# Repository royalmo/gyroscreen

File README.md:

# Gyroscreen

(Work in progress)

A USB device that updates your screen orientation programmatically

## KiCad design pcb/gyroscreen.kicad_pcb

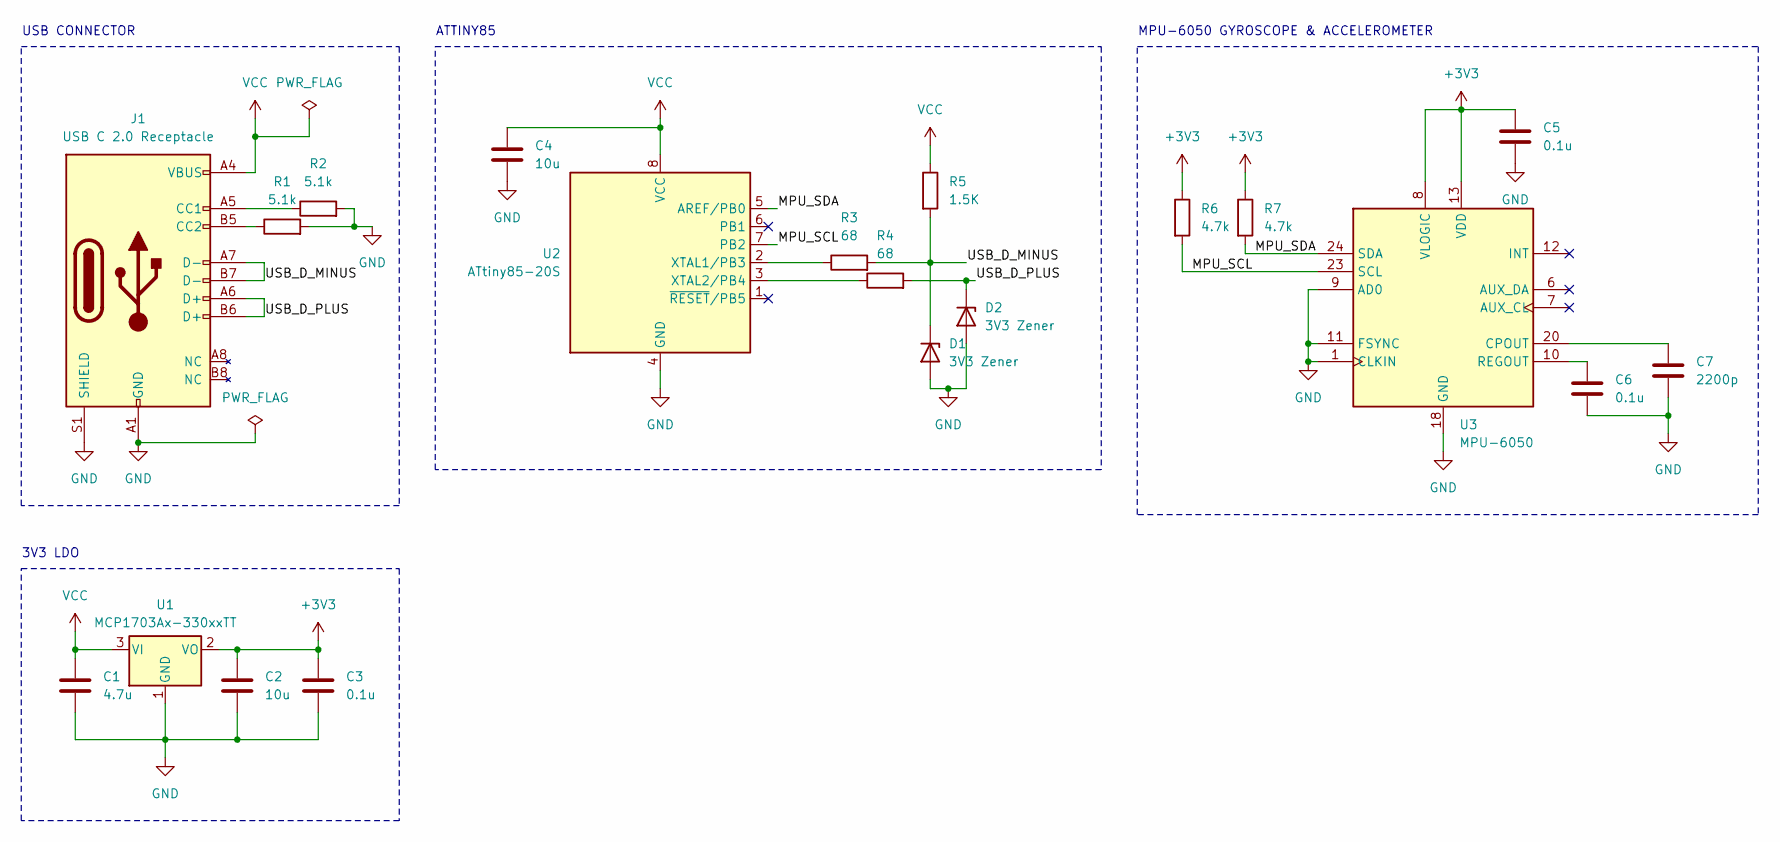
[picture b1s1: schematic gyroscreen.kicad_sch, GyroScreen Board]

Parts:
C1: 4.7u; C_0805_2012Metric_Pad1.18x1.45mm_HandSolder
C2, C4: 10u; C_0805_2012Metric_Pad1.18x1.45mm_HandSolder
C3, C5, C6: 0.1u; C_0805_2012Metric_Pad1.18x1.45mm_HandSolder
C7: 2200p; C_0805_2012Metric_Pad1.18x1.45mm_HandSolder
D1, D2: 3V3 Zener; D_SOD-123F
J1: USB C 2.0 Receptacle; USB_C_Receptacle_G-Switch_GT-USB-7010ASV
R1, R2: 5.1k; R_0805_2012Metric_Pad1.20x1.40mm_HandSolder
R3, R4: 68; R_0805_2012Metric_Pad1.20x1.40mm_HandSolder
R5: 1.5K; R_0805_2012Metric_Pad1.20x1.40mm_HandSolder
R6, R7: 4.7k; R_0805_2012Metric_Pad1.20x1.40mm_HandSolder
U1: MCP1703Ax-330xxTT; SOT-23
U2: ATtiny85-20S; SOIC-8W_5.3x5.3mm_P1.27mm
U3: MPU-6050; InvenSense_QFN-24_4x4mm_P0.5mm

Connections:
+3V3: C2.1, C3.1, C5.1, R6.1, R7.1, U1.2 (VO), U3.8 (VLOGIC), U3.13 (VDD)
/MPU_SCL: R6.2, U2.7 (PB2), U3.23 (SCL)
/MPU_SDA: R7.2, U2.5 (AREF/PB0), U3.24 (SDA)
/USB_D_MINUS: D1.1 (K), J1.A7 (D-), J1.B7 (D-), R3.2, R5.2
/USB_D_PLUS: D2.1 (K), J1.A6 (D+), J1.B6 (D+), R4.2
GND: C1.2, C2.2, C3.2, C4.2, C5.2, C6.2, C7.2, D1.2 (A), D2.2 (A), J1.A1 (GND), J1.A12 (GND), J1.B1 (GND), J1.B12 (GND), J1.S1 (SHIELD), R1.2, R2.2, U1.1 (GND), U2.4 (GND), U3.1 (CLKIN), U3.9 (AD0), U3.11 (FSYNC), U3.18 (GND)
unnamed: J1.A5 (CC1), R2.1
unnamed: J1.B5 (CC2), R1.1
unnamed: R3.1, U2.2 (XTAL1/PB3)
unnamed: R4.1, U2.3 (XTAL2/PB4)
unnamed: C7.1, U3.20 (CPOUT)
unnamed: C6.1, U3.10 (REGOUT)
VCC: C1.1, C4.1, J1.A4 (VBUS), J1.A9 (VBUS), J1.B4 (VBUS), J1.B9 (VBUS), R5.1, U1.3 (VI), U2.8 (VCC)

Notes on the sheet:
MPU-6050 GYROSCOPE & ACCELEROMETER
USB CONNECTOR
ATTINY85
3V3 LDO

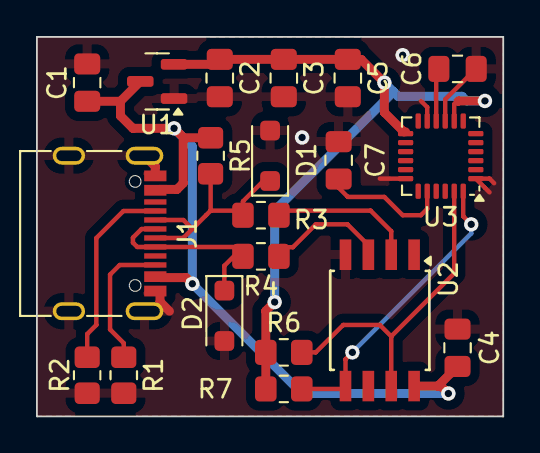
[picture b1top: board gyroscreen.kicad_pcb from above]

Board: 2 copper layers, 25.9 x 21.1 mm, 20 parts (0 on the bottom side), 13 nets.

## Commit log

2024-03-17 Added Gyroscreen PCB rev1
2024-03-17 Temporary readme
2024-03-17 Schematic Revision 2
2024-03-17 PCB without ground layer
2024-03-18 FIlled PCB
2024-03-24 PCB Rev 2.1 sent to print
